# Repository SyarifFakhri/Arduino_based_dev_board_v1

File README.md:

# Arduino_based_dev_board_v1
Custom arduino based development board
Built from KiCad using discrete components, featuring full protection and various slots for electronic plugins

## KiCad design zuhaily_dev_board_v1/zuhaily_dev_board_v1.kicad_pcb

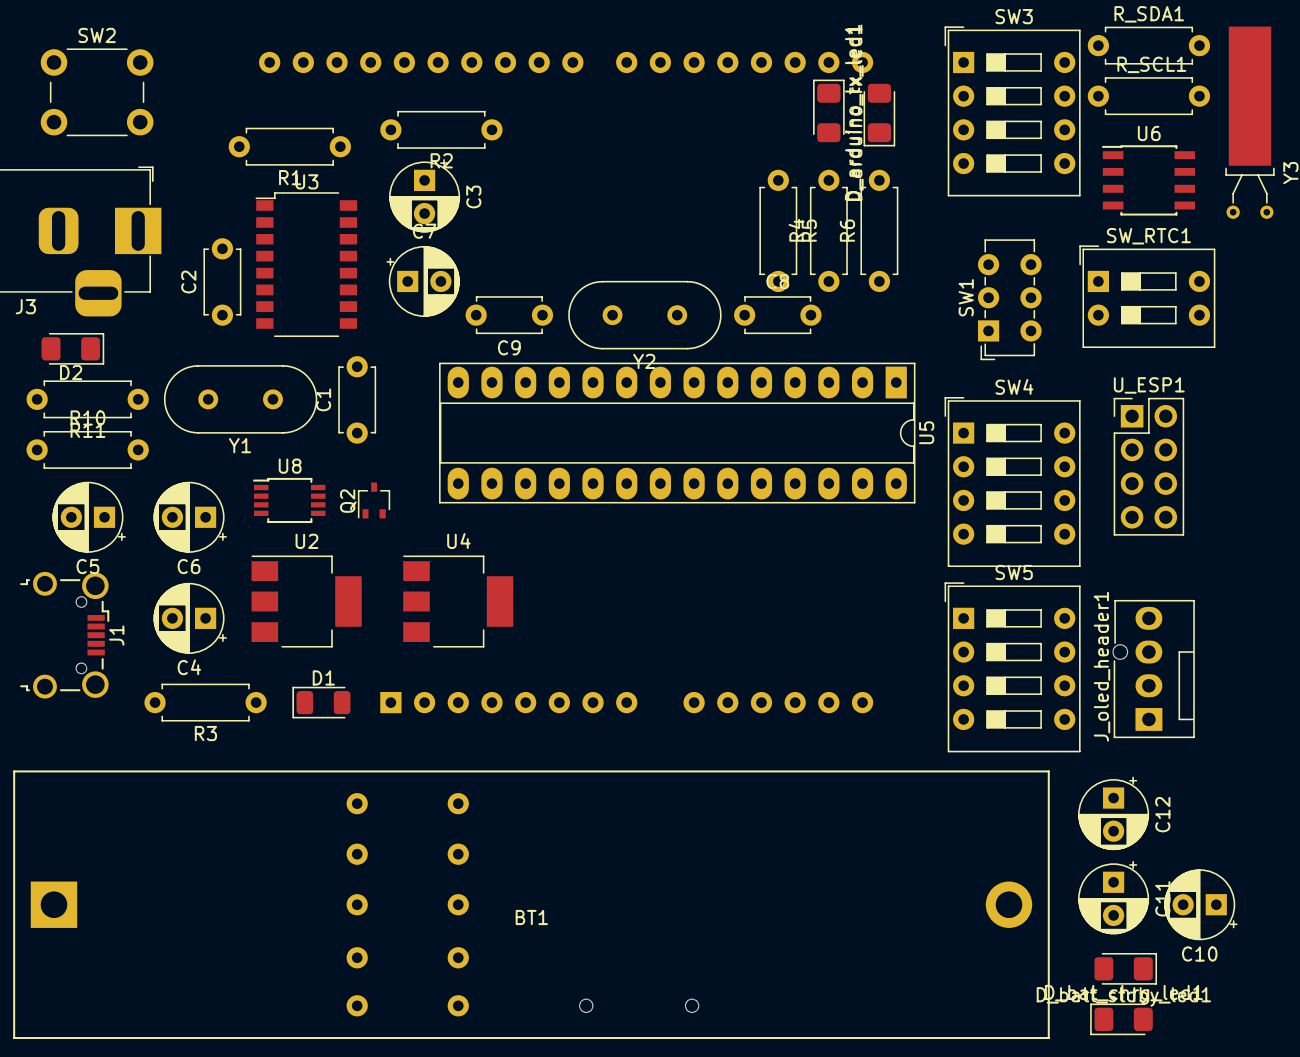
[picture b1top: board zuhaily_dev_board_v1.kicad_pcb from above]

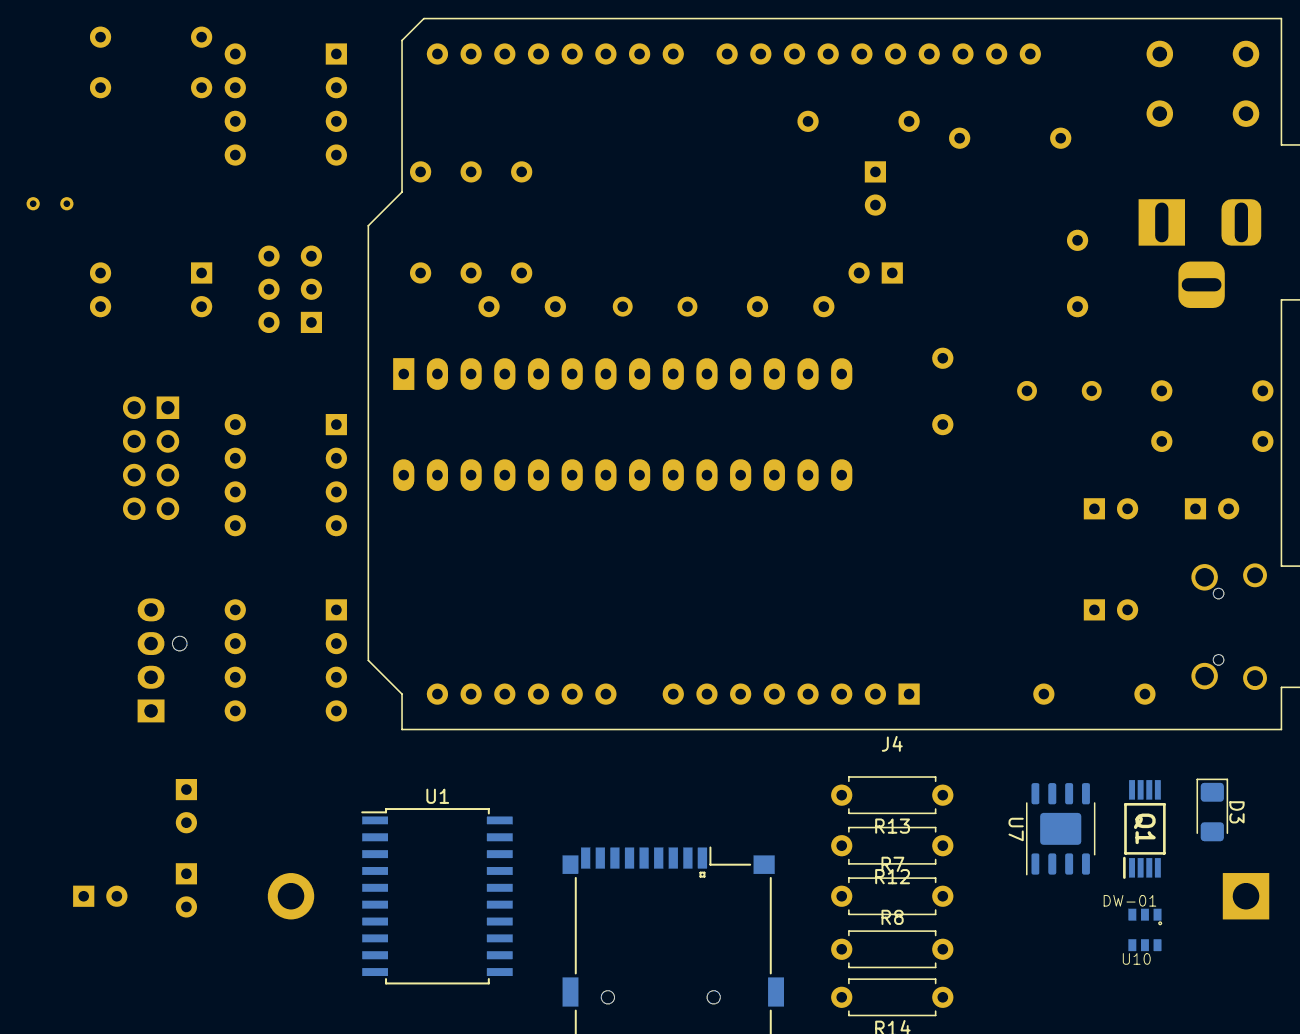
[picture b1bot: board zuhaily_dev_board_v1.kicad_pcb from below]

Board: 2 copper layers, 61 parts (12 on the bottom side), 76 nets, no tracks yet.

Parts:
BT1: Battery_Cell; BatteryHolder_MPD_BH-18650-PC2
C1, C2, C8, C9: 22pF; C_Disc_D4.7mm_W2.5mm_P5.00mm
C3, C7, C10, C12: 0.1uF; CP_Radial_D5.0mm_P2.50mm
C4: 47uF; CP_Radial_D5.0mm_P2.50mm
C5, C6: 100nF; CP_Radial_D5.0mm_P2.50mm
C11: 10uF; CP_Radial_D5.0mm_P2.50mm
D1: LED; LED_1206_3216Metric
D2, D3: D; D_1206_3216Metric_Pad1.42x1.75mm_HandSolder
D_arduino_rx_led1: LED; LED_1206_3216Metric_Pad1.42x1.75mm_HandSolder
D_arduino_tx_led1: LED; LED_1206_3216Metric_Pad1.42x1.75mm_HandSolder
D_bat_chrg_led1: LED; LED_1206_3216Metric_Pad1.42x1.75mm_HandSolder
D_batt_stdby_led1: LED; LED_1206_3216Metric_Pad1.42x1.75mm_HandSolder
J1: USB_B_Micro; USB_Micro-B_Wuerth_629105150521_CircularHoles
J2: Micro_SD_Card; Conn_uSDcard
J3: DC_JACK; BarrelJack_Horizontal
J4: Conn_01x32_Female; Arduino_UNO_R3
J_oled_header1: Conn_01x04_Female; FanPinHeader_1x04_P2.54mm_Vertical
Q1: FS8205A; SOP65P640X120-8N
Q2: FDN340P; SOT-323_SC-70
R1, R2, R3, R4, R6, R7, R8, R14: 1k; R_Axial_DIN0207_L6.3mm_D2.5mm_P7.62mm_Horizontal
R5: 10k; R_Axial_DIN0207_L6.3mm_D2.5mm_P7.62mm_Horizontal
R10, R11: 10K; R_Axial_DIN0207_L6.3mm_D2.5mm_P7.62mm_Horizontal
R12: 2k; R_Axial_DIN0207_L6.3mm_D2.5mm_P7.62mm_Horizontal
R13: 100; R_Axial_DIN0207_L6.3mm_D2.5mm_P7.62mm_Horizontal
R_SCL1: 10k; R_Axial_DIN0207_L6.3mm_D2.5mm_P7.62mm_Horizontal
R_SDA1: 10k; R_Axial_DIN0207_L6.3mm_D2.5mm_P7.62mm_Horizontal
SW1: SW_DPDT_x2; SW_E-Switch_EG1271_DPDT
SW2: SW_SPST; SW_PUSH_6mm_H4.3mm
SW3, SW4, SW5: SW_DIP_x04; SW_DIP_SPSTx04_Slide_9.78x12.34mm_W7.62mm_P2.54mm
SW_RTC1: SW_DIP_x02; SW_DIP_SPSTx02_Slide_9.78x7.26mm_W7.62mm_P2.54mm
U1: 74LVC245; SOIC-20W_7.5x12.8mm_P1.27mm
U2: LM1117-5.0; SOT-223
U3: CH340G; SOP-16_4.4x10.4mm_P1.27mm
U4: LM1117-3.3; SOT-223
U5: ATmega328-PU; DIP-28_W7.62mm_Socket_LongPads
U6: DS1307Z+; SOIC-8_3.9x4.9mm_P1.27mm
U7: TP4056; HSOP-8-1EP_3.9x4.9mm_P1.27mm_EP2.41x3.1mm
U8: LMV358; TSSOP-8_3x3mm_P0.65mm
U10: DW-01; SOT23-6
U_ESP1: ESP-01v090; PinHeader_2x04_P2.54mm_Vertical
Y1: Crystal_12MHz; Crystal_HC49-4H_Vertical
Y2: Crystal_16MHz; Crystal_HC49-4H_Vertical
Y3: Crystal_GND3; Crystal_AT310_D3.0mm_L10.0mm_Horizontal_1EP_style1

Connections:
/3.3V_REGULATED: J2.4, J4.4, SW4.3, U1.1, U1.20, U4.2, U8.2
/5V_FILTERED: C3.1, C4.1, C5.1, C6.1, C10.1, D1.2, D3.1, D_bat_chrg_led1.2, D_batt_stdby_led1.2, J4.2, J4.5, J4.8, J4.30, Q2.3, R4.1, R5.2, R6.1, R_SCL1.1, R_SDA1.1, SW5.1, U2.2, U3.16, U4.3, U5.7, U5.20, U5.21, U6.3, U6.8, U7.4, U7.8, U8.8
/5V_REGULATOR_IN: D2.1, R10.1, U2.3
/ARDUINO_CRYSTAL_1: C8.1, U5.9, Y2.1
/ARDUINO_CRYSTAL_2: C9.1, U5.10, Y2.2
/ARDUINO_LEVEL_SHIFT_CS: J4.25, SW3.2, U5.16
/ARDUINO_LEVEL_SHIFT_MOSI: J4.26, SW3.3, U5.17
/ARDUINO_LEVEL_SHIFT_SCK: J4.28, SW3.1, U5.19
/ARDUINO_RESET: C7.2, J4.3, R5.1, SW2.1, U5.1
/ARDUINO_RX: D_arduino_rx_led1.1, J4.15, SW1.1, U5.2
/ARDUINO_SD_MISO: J4.27, SW3.4, U5.18
/ARDUINO_TX: D_arduino_tx_led1.1, J4.16, SW1.4, U5.3
/BATT_OUT_POSITIVE: BT1.1, C11.1, D3.2, R13.1, U7.5
/CH340_DTR: C7.1, U3.13
/D_MINUS: J1.2, U3.6
/D_PLUS: J1.3, U3.5
/ESP_RX: SW1.3, SW4.2
/ESP_TX: SW1.6, SW4.1
/LED_CHRG: R8.2, U7.7
/LED_STDBY: R7.2, U7.6
/LEVEL_SHIFT_SD_CS: J2.2, U1.14
/LEVEL_SHIFT_SD_MOSI: J2.3, U1.13
/LEVEL_SHIFT_SD_SCK: J2.5, U1.15
/PB_0: J4.23, U5.14
/PB_1: J4.24, U5.15
/PC_0: J4.9, U5.23
/PC_1: J4.10, U5.24
/PC_2: J4.11, U5.25
/PC_3: J4.12, U5.26
/PC_4: J4.13, J4.31, SW5.4, SW_RTC1.2, U5.27
/PC_5: J4.14, J4.32, SW5.3, SW_RTC1.1, U5.28
/PD_2: J4.17, U5.4
/PD_3: J4.18, U5.5
/PD_4: J4.19, U5.6
/PD_5: J4.20, U5.11
/PD_6: J4.21, U5.12
/PD_7: J4.22, U5.13
/USB_VCC: J1.1, Q2.2
GND: C1.2, C2.2, C4.2, C5.2, C6.2, C8.2, C9.2, C10.2, C11.2, J1.5, J1.6, J2.6, J2.9, J3.1, J3.3, J4.6, J4.7, J4.29, Q1.6, Q1.7, R3.2, R11.2, R12.2, R14.2, SW2.2, SW4.4, SW5.2, U1.10, U1.19, U2.1, U3.1, U4.1, U5.8, U5.22, U6.4, U7.1, U7.3, U8.4, Y3.3
unnamed: BT1.2, C12.2, Q1.2, Q1.3, U10.6
unnamed: C1.1, U3.7, Y1.1
unnamed: C2.1, U3.8, Y1.2
unnamed: C3.2, U3.4
unnamed: C12.1, R13.2, U10.5
unnamed: D1.1, R3.1
unnamed: D2.2, J3.2
unnamed: D_arduino_rx_led1.2, R6.2
unnamed: D_arduino_tx_led1.2, R4.2
unnamed: D_bat_chrg_led1.1, R8.1
unnamed: D_batt_stdby_led1.1, R7.1
unnamed: J2.7, SW3.5
unnamed: J_oled_header1.1, SW5.5
unnamed: J_oled_header1.2, SW5.6
unnamed: J_oled_header1.3, SW5.7
unnamed: J_oled_header1.4, SW5.8
unnamed: Q1.4, U10.1
unnamed: Q1.5, U10.3
unnamed: Q2.1, U8.1
unnamed: R1.1, SW1.2
unnamed: R1.2, U3.2
unnamed: R2.1, SW1.5
unnamed: R2.2, U3.3
unnamed: R10.2, R11.1, U8.3
unnamed: R12.1, U7.2
unnamed: R14.1, U10.2
unnamed: R_SCL1.2, SW_RTC1.4, U6.6
unnamed: R_SDA1.2, SW_RTC1.3, U6.5
unnamed: SW3.6, U1.7
unnamed: SW3.7, U1.6
unnamed: SW3.8, U1.5
unnamed: SW4.5, U_ESP1.2
unnamed: SW4.6, U_ESP1.7
unnamed: SW4.7, U_ESP1.8
unnamed: SW4.8, U_ESP1.1
unnamed: U6.1, Y3.1
unnamed: U6.2, Y3.2

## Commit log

2019-01-29 added battery protection ic and testing git
2019-01-29 branch commit
2019-01-29 removed test branch changes
2019-01-30 added dc/usb switcher
2019-01-30 added part of battery protection ic and some initial wiring
2019-02-04 added battery protection - dwa01
2019-02-04 corrected some changes in the battery protect circuit
2019-02-04 finished schematic started pcb design
2019-02-06 generated pcb
2019-02-06 changed battery holder
2019-02-06 added images
2019-02-06 added rtc
2019-03-21 working version without headers
2019-03-21 changed the esp, ds1307 and sd card to header outputs
